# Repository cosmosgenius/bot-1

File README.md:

Bot 1
==========

This repo contains source of a simple rc bot.

Boards - This folder contains all the circuit diagrams and PCBS developed in building the bot
Mark-X - X is the Xth version of the bot. These folder contains the source code for the bot.

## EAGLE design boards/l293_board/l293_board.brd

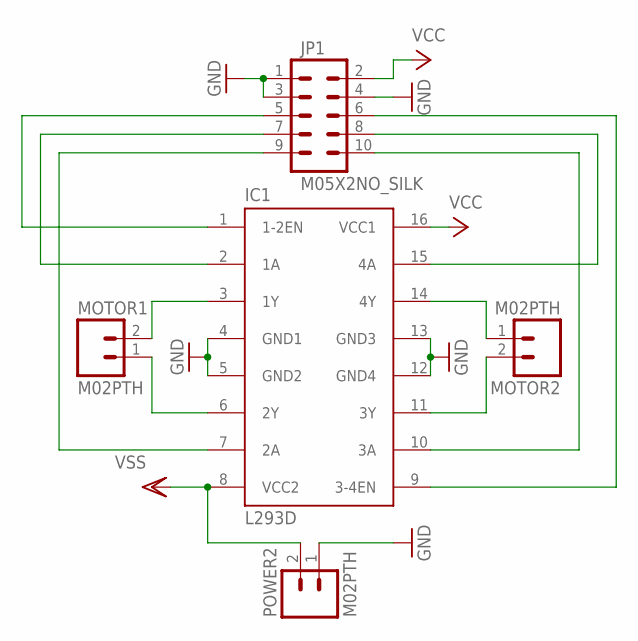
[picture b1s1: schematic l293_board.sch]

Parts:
IC1: L293D; DIL16
JP1: M05X2NO_SILK; 2X5_NOSILK
MOTOR1, MOTOR2: M02PTH; 1X02
POWER2: M02PTH; 1X02

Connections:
GND: IC1.4 (GND1), IC1.5 (GND2), IC1.12 (GND4), IC1.13 (GND3), JP1.1, JP1.3, JP1.4, POWER2.1
unnamed: IC1.9 (3-4EN), JP1.6
unnamed: IC1.1 (1-2EN), JP1.5
unnamed: IC1.3 (1Y), MOTOR1.2
unnamed: IC1.6 (2Y), MOTOR1.1
unnamed: IC1.15 (4A), JP1.8
unnamed: IC1.2 (1A), JP1.7
unnamed: IC1.7 (2A), JP1.9
unnamed: IC1.14 (4Y), MOTOR2.1
unnamed: IC1.11 (3Y), MOTOR2.2
unnamed: IC1.10 (3A), JP1.10
VCC: IC1.16 (VCC1), JP1.2
VSS: IC1.8 (VCC2), POWER2.2

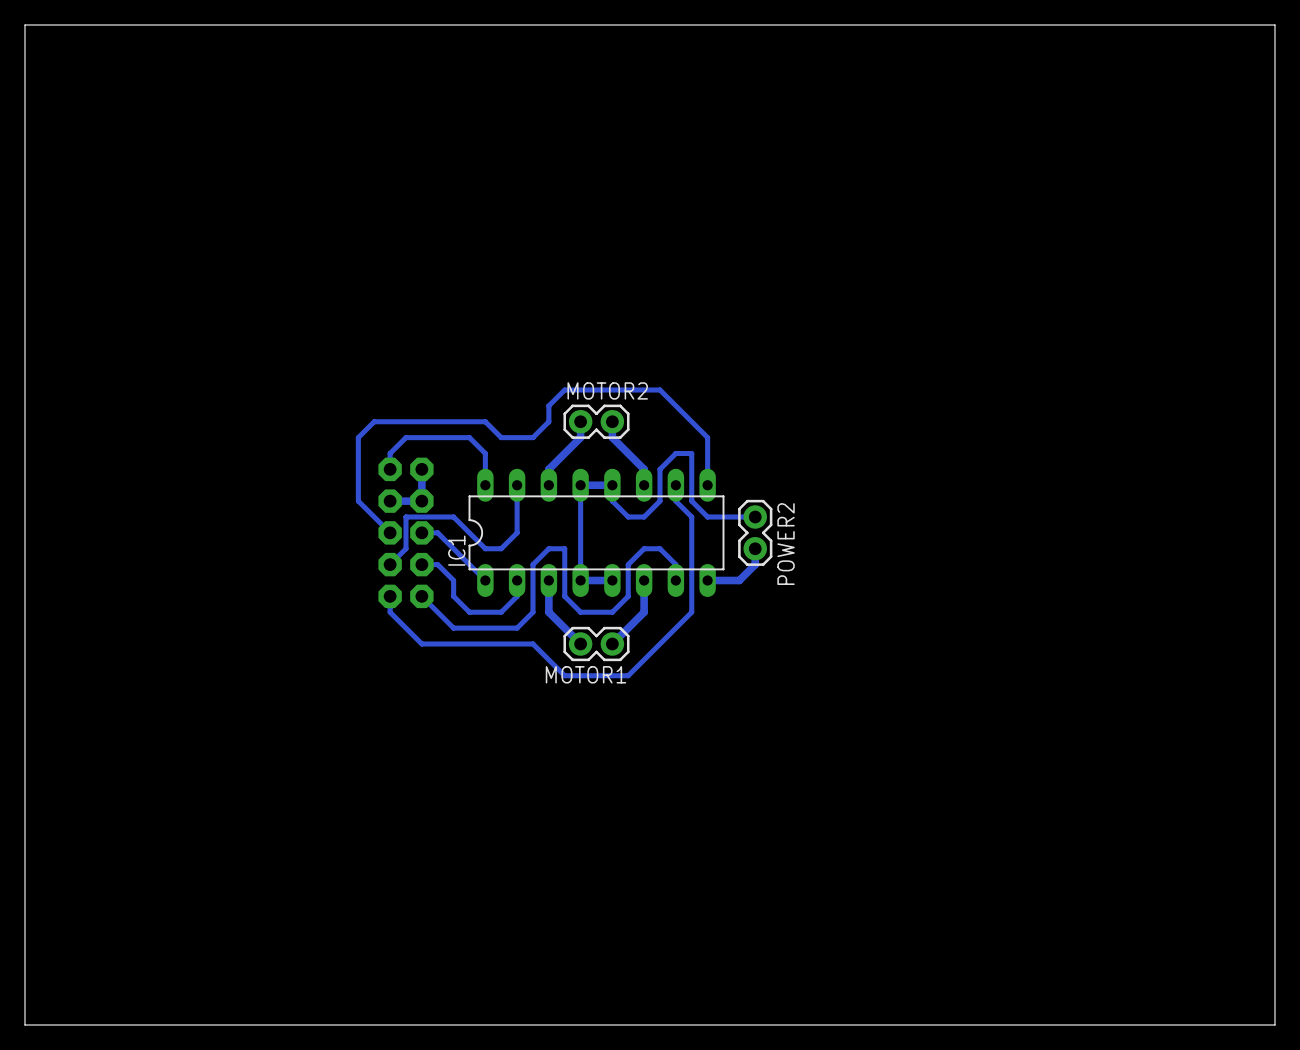
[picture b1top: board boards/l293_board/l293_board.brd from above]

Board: 2 copper layers, 100.0 x 80.0 mm, 5 parts (1 on the bottom side), 13 nets.

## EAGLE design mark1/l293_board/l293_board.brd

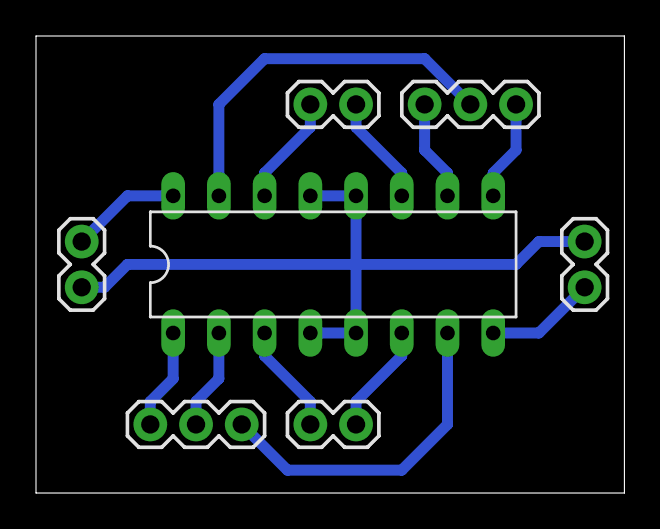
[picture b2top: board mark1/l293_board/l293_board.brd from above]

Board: 2 copper layers, 32.7 x 25.4 mm, 7 parts (0 on the bottom side), 13 nets.

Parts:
CON_MOTOR1, CON_MOTOR2: 1X03
IC1: L293D; DIL16
MOTOR1, MOTOR2: M02PTH; 1X02
POWER1, POWER2: M02PTH; 1X02

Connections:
GND: IC1.4, IC1.5, IC1.12, IC1.13, POWER1.1, POWER2.1
unnamed: CON_MOTOR2.1, IC1.9
unnamed: CON_MOTOR1.3, IC1.1
unnamed: IC1.3, MOTOR1.2
unnamed: IC1.6, MOTOR1.1
unnamed: CON_MOTOR2.2, IC1.15
unnamed: CON_MOTOR1.2, IC1.2
unnamed: CON_MOTOR1.1, IC1.7
unnamed: IC1.14, MOTOR2.1
unnamed: IC1.11, MOTOR2.2
unnamed: CON_MOTOR2.3, IC1.10
VCC: IC1.16, POWER1.2
VSS: IC1.8, POWER2.2

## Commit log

2014-11-05 added mark1 file
2014-11-05 added speed control using pwm
2014-11-05 added circuit
2014-11-05 some modification to layers
2014-11-10 added two enable pins
2014-11-10 moved the board to boards folder
2014-11-10 added a makefile
2014-11-11 del makefile
2014-11-11 moved to cmake
2014-11-15 moved to make agaign
2014-11-15 updated makefile and moved the F_CPU to make
2014-11-15 removed unwanted parts from makefile
2014-11-15 add some variable to makefile
2014-11-15 Made F_CPU to unsigned long
2014-11-15 updated gitignore
2014-11-15 added avrdude upload option
2014-11-15 removed MCU_TYPE variable from makefile
2014-11-17 added tinkerer's rf24 lib
2014-11-17 some correction to the interrupt vector implementation
2014-11-18 updated board to make 5x2 connector
2014-11-18 removed the rf24 lib
2014-11-18 moved to 2 tab spaces
2014-11-18 moved to cpp
2014-11-18 added wheel class
2014-11-20 added initial code

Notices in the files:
parts and their libraries:
SparkFun-Connectors: Licensing: Creative Commons ShareAlike 4.0 International - https://creativecommons.org/licenses/by-sa/4.0
